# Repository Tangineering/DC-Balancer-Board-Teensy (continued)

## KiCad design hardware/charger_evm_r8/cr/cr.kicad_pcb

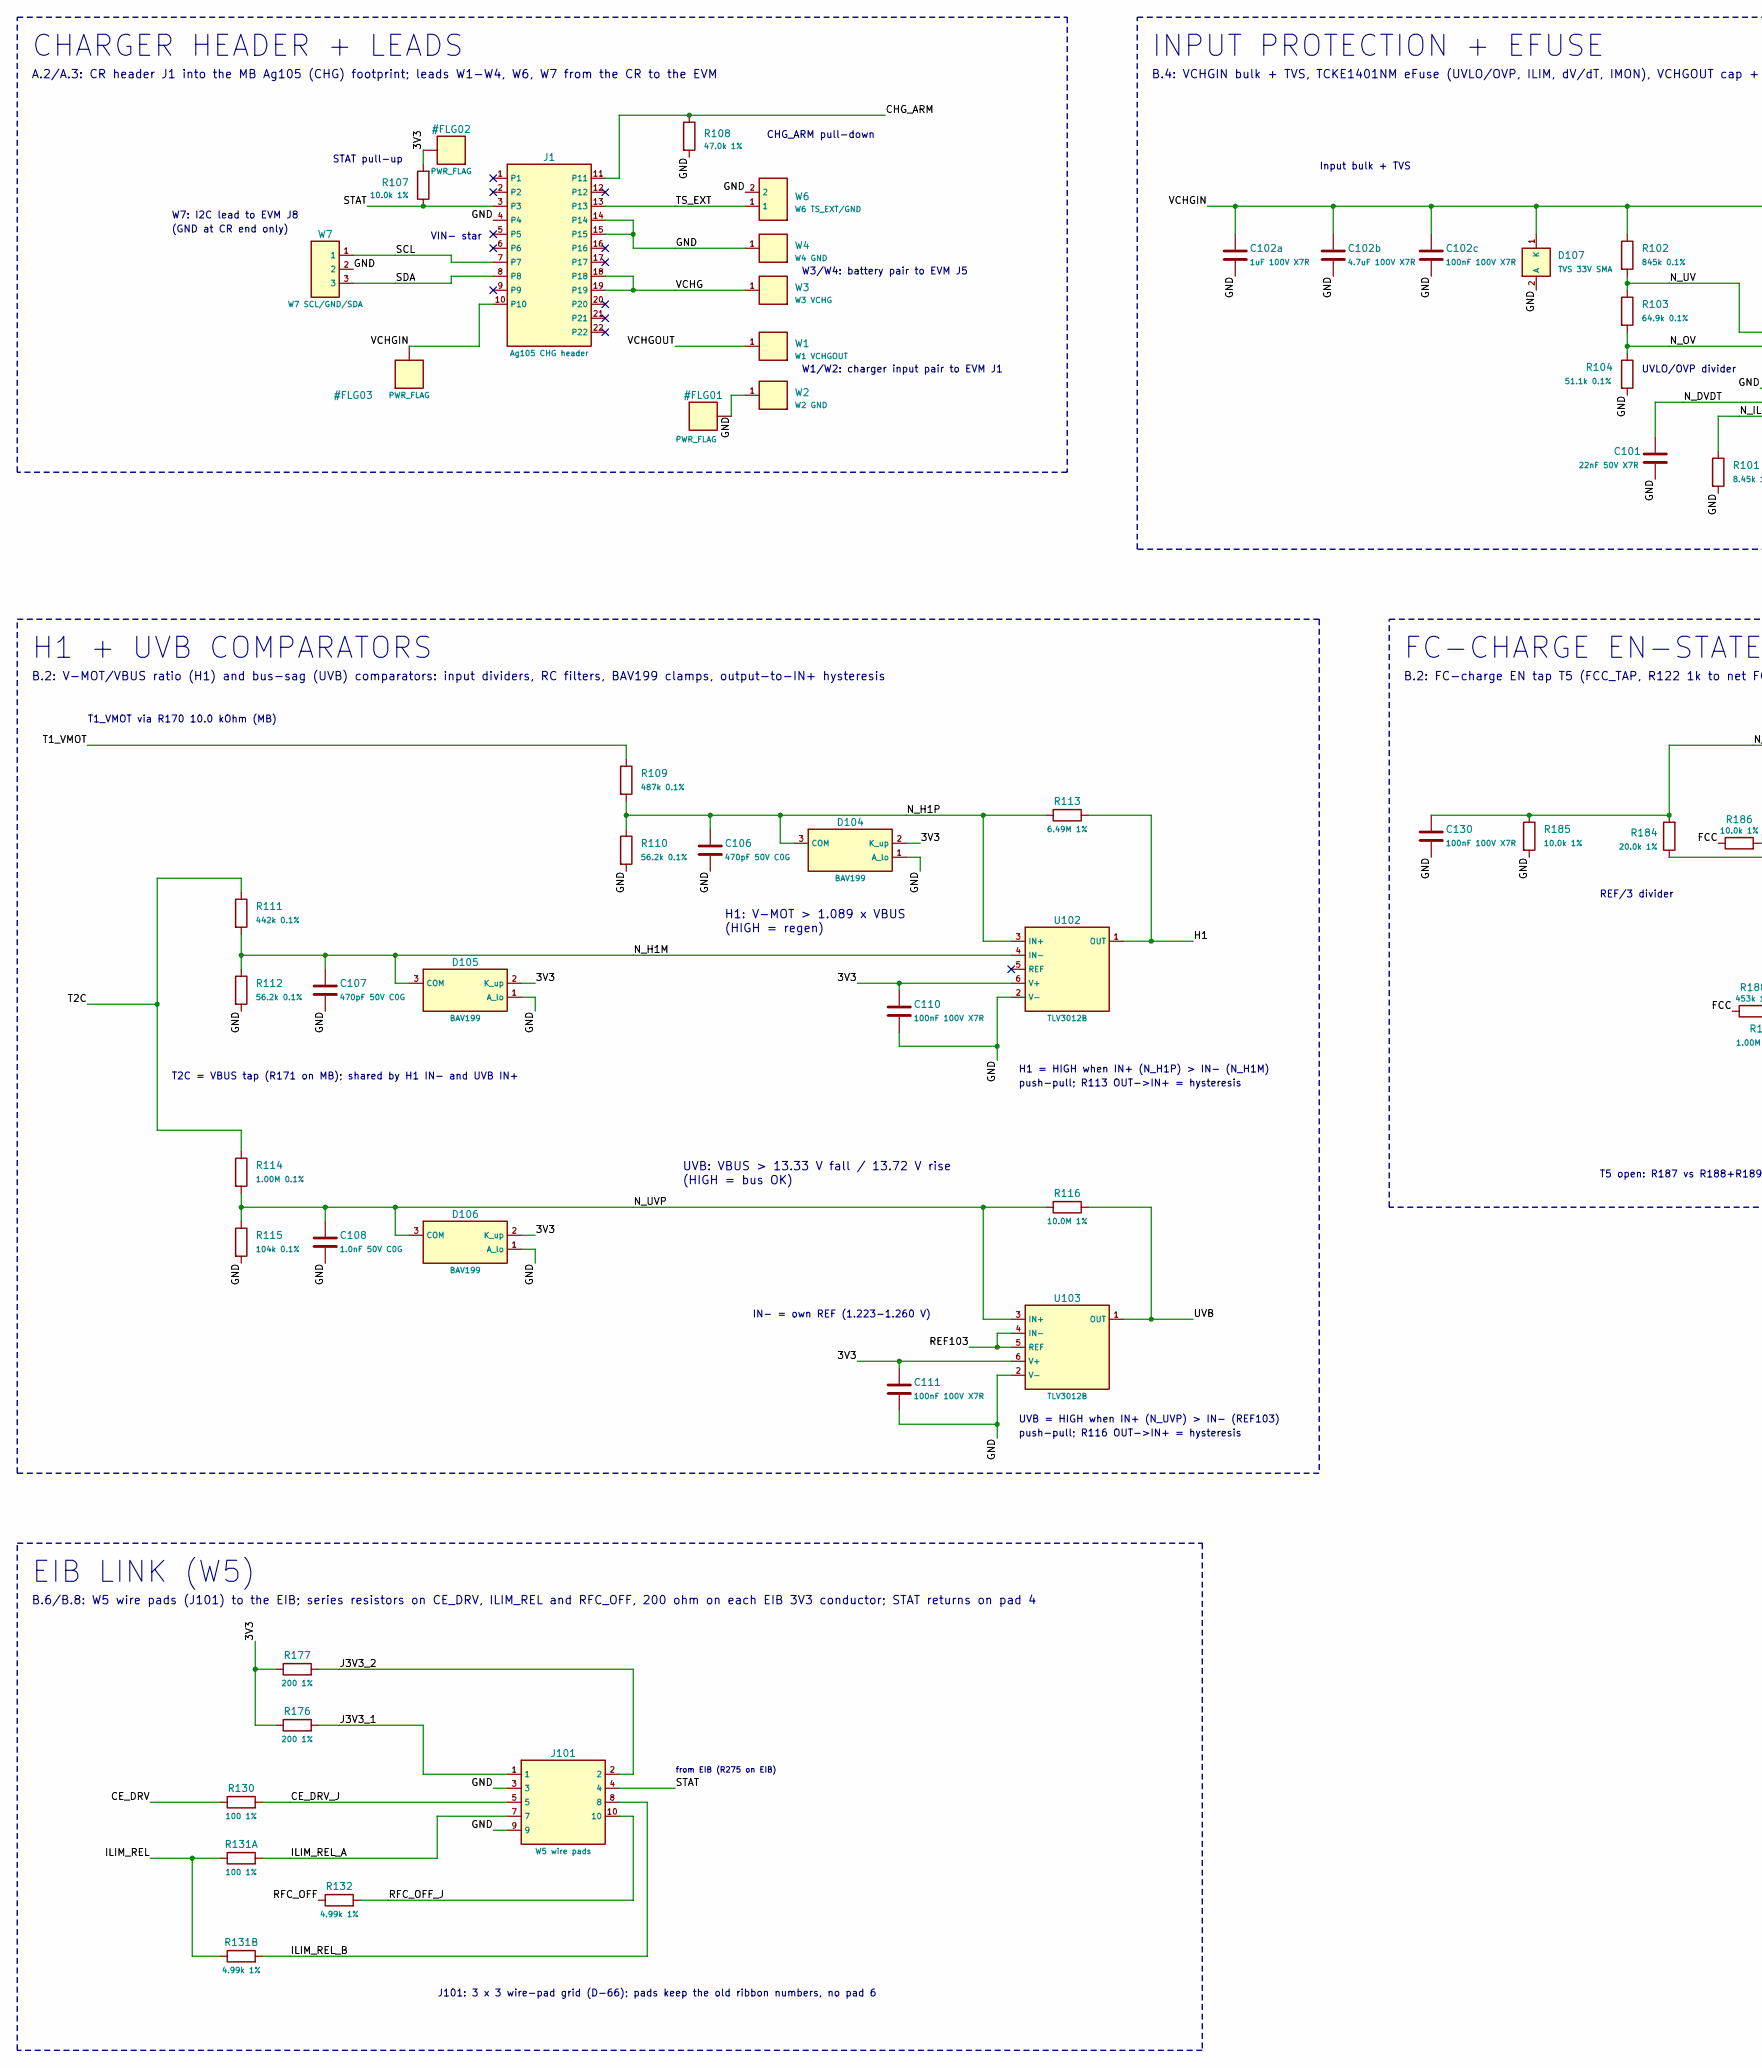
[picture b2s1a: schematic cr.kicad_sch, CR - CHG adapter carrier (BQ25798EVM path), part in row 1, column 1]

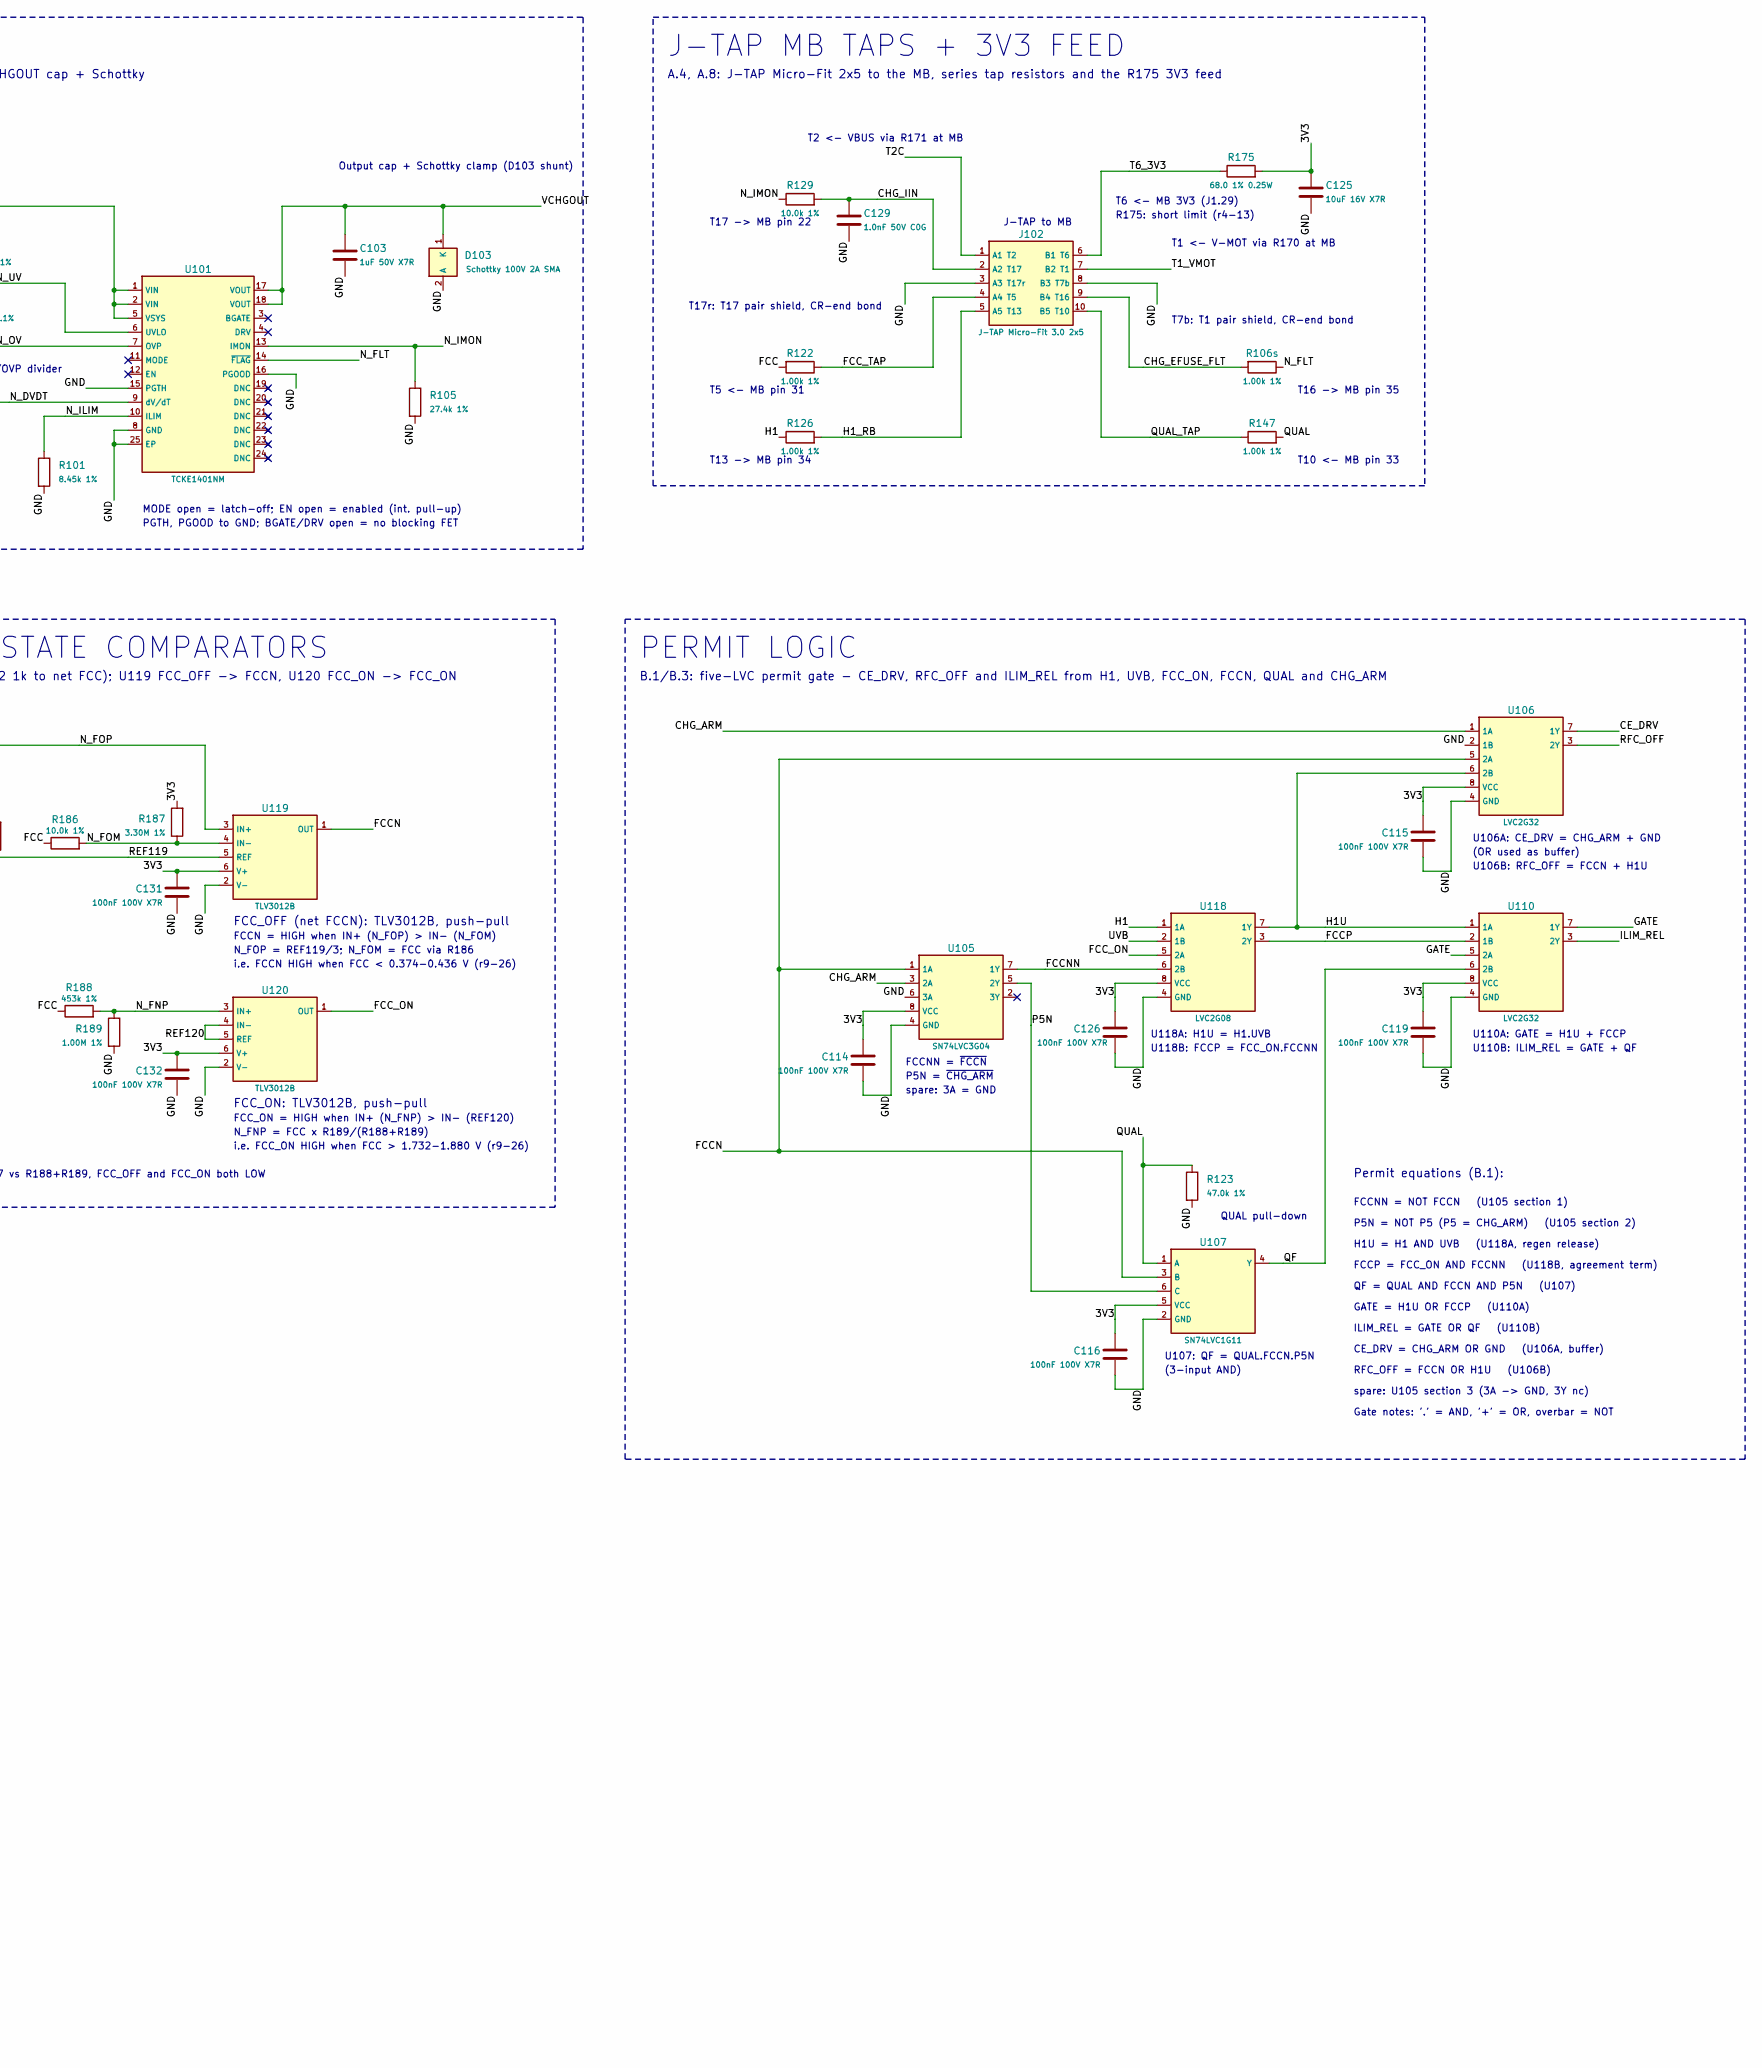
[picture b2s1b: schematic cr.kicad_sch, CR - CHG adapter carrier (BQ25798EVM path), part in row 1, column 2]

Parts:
C101: 22nF 50V X7R; C_0603_1608Metric_CrtYd0.25; MPN C0603C223K5RACTU
C102a: 1uF 100V X7R; C_1206_3216Metric_CrtYd0.25; MPN CL31B105KCHSFNE
C102b: 4.7uF 100V X7R; C_1210_3225Metric_CrtYd0.25; MPN CNC6P1X7R2A475K250AE
C102c, C110, C111, C114, C115, C116, C119, C126, C130, C131, C132: 100nF 100V X7R; C_0603_1608Metric_CrtYd0.25; MPN GRM188R72A104KA35D
C103: 1uF 50V X7R; C_0805_2012Metric_CrtYd0.25; MPN CL21B105KBFNNNF
C106, C107: 470pF 50V C0G; C_0603_1608Metric_CrtYd0.25; MPN GRM1885C1H471JA01D
C108, C129: 1.0nF 50V C0G; C_0603_1608Metric_CrtYd0.25; MPN GRM1885C1H102JA01D
C125: 10uF 16V X7R; C_0805_2012Metric_CrtYd0.25; MPN CL21B106KOQNNNE
D103: Schottky 100V 2A SMA; D_SMA_CrtYd0.25; MPN STPS2H100A
D104, D105, D106: BAV199; SOT-23_CrtYd0.25; MPN BAV199-7-F
D107: TVS 33V SMA; D_SMA_CrtYd0.25; MPN SMAJ33A
J1: Ag105 CHG header; Ag105_CHG_Carrier_22pin_P2.54mm; MPN TSW-110-07-L-S + TSW-112-07-L-S
J101: W5 wire pads; WirePads_PTH_3x3_D1.0mm_Pad1.8mm_P2.54mm_CrtYd0.25
J102: J-TAP Micro-Fit 3.0 2x5; Molex_Micro-Fit_3.0_43045-1012_2x05_P3.00mm_Vertical_CrtYd0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; MPN 43045-1012
R101: 8.45k 1%; R_0603_1608Metric_CrtYd0.25; MPN CRCW06038K45FKEA
R102: 845k 0.1%; R_0805_2012Metric_CrtYd0.25; MPN ERA-6AEB8453V
R103: 64.9k 0.1%; R_0603_1608Metric_CrtYd0.25; MPN ERA-3AEB6492V
R104: 51.1k 0.1%; R_0603_1608Metric_CrtYd0.25; MPN TNPW060351K1BEEA
R105: 27.4k 1%; R_0603_1608Metric_CrtYd0.25; MPN CRCW060327K4FKEA
R106s, R122, R126, R147: 1.00k 1%; R_0603_1608Metric_CrtYd0.25; MPN CRCW06031K00FKEA
R107, R129, R185, R186: 10.0k 1%; R_0603_1608Metric_CrtYd0.25; MPN CRCW060310K0FKEA
R108, R123: 47.0k 1%; R_0603_1608Metric_CrtYd0.25; MPN CRCW060347K0FKEA
R109: 487k 0.1%; R_0805_2012Metric_CrtYd0.25; MPN ERA-6AEB4873V
R110, R112: 56.2k 0.1%; R_0603_1608Metric_CrtYd0.25; MPN ERA-3AEB5622V
R111: 442k 0.1%; R_0805_2012Metric_CrtYd0.25; MPN TNPW0805442KBEEA
R113: 6.49M 1%; R_0603_1608Metric_CrtYd0.25; MPN CRCW06036M49FKEA
R114: 1.00M 0.1%; R_0805_2012Metric_CrtYd0.25; MPN TNPW08051M00BEEA
R115: 104k 0.1%; R_0603_1608Metric_CrtYd0.25; MPN RT0603BRD07104KL
R116: 10.0M 1%; R_0603_1608Metric_CrtYd0.25; MPN CRCW060310M0FKEA
R130, R131A: 100 1%; R_0603_1608Metric_CrtYd0.25; MPN CRCW0603100RFKEA
R131B, R132: 4.99k 1%; R_0603_1608Metric_CrtYd0.25; MPN CRCW06034K99FKEA
R175: 68.0 1% 0.25W; R_1206_3216Metric_CrtYd0.25; MPN CRCW120668R0FKEA
R176, R177: 200 1%; R_0603_1608Metric_CrtYd0.25; MPN CRCW0603200RFKEA
R184: 20.0k 1%; R_0603_1608Metric_CrtYd0.25; MPN CRCW060320K0FKEA
R187: 3.30M 1%; R_0603_1608Metric_CrtYd0.25; MPN CRCW06033M30FKEA
R188: 453k 1%; R_0603_1608Metric_CrtYd0.25; MPN CRCW0603453KFKEA
R189: 1.00M 1%; R_0603_1608Metric_CrtYd0.25; MPN CRCW06031M00FKEA
U101: TCKE1401NM; TPS26630_RGE0024_VQFN-24_4x4mm_P0.5mm_ThermalVias_CrtYd0.25; MPN TCKE1401NM,R1F
U102, U103, U119, U120: TLV3012B; SOT-23-6_CrtYd0.25; MPN TLV3012BIDBVR
U105: SN74LVC3G04; Texas_DCT0008A_SSOP-8_TI-land_CrtYd0.25; MPN SN74LVC3G04DCTR
U106, U110: LVC2G32; Texas_DCT0008A_SSOP-8_TI-land_CrtYd0.25; MPN SN74LVC2G32DCTR
U107: SN74LVC1G11; SOT-23-6_CrtYd0.25; MPN SN74LVC1G11DBVR
U118: LVC2G08; Texas_DCT0008A_SSOP-8_TI-land_CrtYd0.25; MPN SN74LVC2G08IDCTRQ1
W1: W1 VCHGOUT; LeadPad_PTH_D1.3mm_Pad2.3mm_CrtYd0.25
W2: W2 GND; LeadPad_PTH_D1.3mm_Pad2.3mm_CrtYd0.25
W3: W3 VCHG; LeadPad_PTH_D1.5mm_Pad2.5mm_CrtYd0.25
W4: W4 GND; LeadPad_PTH_D1.5mm_Pad2.5mm_CrtYd0.25
W6: W6 TS_EXT/GND; LeadPads_PTH_1x02_D1.0mm_Pad1.8mm_P2.54mm_Placeholder
W7: W7 SCL/GND/SDA; LeadPads_PTH_1x03_D1.0mm_Pad1.8mm_P2.54mm_Placeholder

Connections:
/3V3: C110.1, C111.1, C114.1, C115.1, C116.1, C119.1, C125.1, C126.1, C131.1, C132.1, D104.2 (K_up), D105.2 (K_up), D106.2 (K_up), R107.2, R175.2, R176.1, R177.1, R187.2, U102.6 (V+), U103.6 (V+), U105.8 (VCC), U106.8 (VCC), U107.5 (VCC), U110.8 (VCC), U118.8 (VCC), U119.6 (V+), U120.6 (V+)
/CE_DRV: R130.1, U106.7 (1Y)
/CE_DRV_J: J101.5, R130.2
/CHG_ARM: J1.11, R108.1, U105.3 (2A), U106.1 (1A)
/CHG_EFUSE_FLT: J102.9 (B4 T16), R106s.2
/CHG_IIN: C129.1, J102.2 (A2 T17), R129.2
/FCC: R122.2, R186.1, R188.1
/FCCN: U105.1 (1A), U106.5 (2A), U107.3 (B), U119.1 (OUT)
/FCCNN: U105.7 (1Y), U118.6 (2B)
/FCCP: U110.2 (1B), U118.3 (2Y)
/FCC_ON: U118.5 (2A), U120.1 (OUT)
/FCC_TAP: J102.4 (A4 T5), R122.1
/GATE: U110.5 (2A), U110.7 (1Y)
/GND: C101.2, C102a.2, C102b.2, C102c.2, C103.2, C106.2, C107.2, C108.2, C110.2, C111.2, C114.2, C115.2, C116.2, C119.2, C125.2, C126.2, C129.2, C130.2, C131.2, C132.2, D103.2 (A), D104.1 (A_lo), D105.1 (A_lo), D106.1 (A_lo), D107.2 (A), J1.4, J1.14, J1.15, J101.3, J101.9, J102.3 (A3 T17r), J102.8 (B3 T7b), R101.2, R104.2, R105.2, R108.2, R110.2, R112.2, R115.2, R123.2, R185.2, R189.2, U101.8 (GND), U101.15 (PGTH), U101.16 (PGOOD), U101.25 (EP), U102.2 (V-), U103.2 (V-), U105.4 (GND), U105.6 (3A), U106.2 (1B), U106.4 (GND), U107.2 (GND), U110.4 (GND), U118.4 (GND), U119.2 (V-), U120.2 (V-), W2.1, W4.1, W6.2, W7.2
/H1: R113.1, R126.1, U102.1 (OUT), U118.1 (1A)
/H1U: U106.6 (2B), U110.1 (1A), U118.7 (1Y)
/H1_RB: J102.5 (A5 T13), R126.2
/ILIM_REL: R131A.1, R131B.1, U110.3 (2Y)
/ILIM_REL_A: J101.7, R131A.2
/ILIM_REL_B: J101.8, R131B.2
/J3V3_1: J101.1, R176.2
/J3V3_2: J101.2, R177.2
/N_DVDT: C101.1, U101.9 (dV/dT)
/N_FLT: R106s.1, U101.14 (~FLAG)
/N_FNP: R188.2, R189.1, U120.3 (IN+)
/N_FOM: R186.2, R187.1, U119.4 (IN-)
/N_FOP: C130.1, R184.2, R185.1, U119.3 (IN+)
/N_H1M: C107.1, D105.3 (COM), R111.2, R112.1, U102.4 (IN-)
/N_H1P: C106.1, D104.3 (COM), R109.2, R110.1, R113.2, U102.3 (IN+)
/N_ILIM: R101.1, U101.10 (ILIM)
/N_IMON: R105.1, R129.1, U101.13 (IMON)
/N_OV: R103.2, R104.1, U101.7 (OVP)
/N_UV: R102.2, R103.1, U101.6 (UVLO)
/N_UVP: C108.1, D106.3 (COM), R114.2, R115.1, R116.2, U103.3 (IN+)
/P5N: U105.5 (2Y), U107.6 (C)
/QF: U107.4 (Y), U110.6 (2B)
/QUAL: R123.1, R147.2, U107.1 (A)
/QUAL_TAP: J102.10 (B5 T10), R147.1
/REF103: U103.4 (IN-), U103.5 (REF)
/REF119: R184.1, U119.5 (REF)
/REF120: U120.4 (IN-), U120.5 (REF)
/RFC_OFF: R132.1, U106.3 (2Y)
/RFC_OFF_J: J101.10, R132.2
/SCL: J1.7, W7.1
/SDA: J1.8, W7.3
/STAT: J1.3, J101.4, R107.1
/T1_VMOT: J102.7 (B2 T1), R109.1
/T2C: J102.1 (A1 T2), R111.1, R114.1
/T6_3V3: J102.6 (B1 T6), R175.1
/TS_EXT: J1.13, W6.1
/UVB: R116.1, U103.1 (OUT), U118.2 (1B)
/VCHG: J1.18, J1.19, W3.1
/VCHGIN: C102a.1, C102b.1, C102c.1, D107.1 (K), J1.10, R102.1, U101.1 (VIN), U101.2 (VIN), U101.5 (VSYS)
/VCHGOUT: C103.1, D103.1 (K), U101.17 (VOUT), U101.18 (VOUT), W1.1

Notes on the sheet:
CHARGER HEADER + LEADS
A.2/A.3: CR header J1 into the MB Ag105 (CHG) footprint; leads W1-W4, W6, W7 from the CR to the EVM
STAT pull-up
CHG_ARM pull-down
W7: I2C lead to EVM J8
(GND at CR end only)
W1/W2: charger input pair to EVM J1
W3/W4: battery pair to EVM J5
VIN- star
INPUT PROTECTION + EFUSE
B.4: VCHGIN bulk + TVS, TCKE1401NM eFuse (UVLO/OVP, ILIM, dV/dT, IMON), VCHGOUT cap + Schottky
Input bulk + TVS
UVLO/OVP divider
Output cap + Schottky clamp (D103 shunt)
MODE open = latch-off; EN open = enabled (int. pull-up)
PGTH, PGOOD to GND; BGATE/DRV open = no blocking FET
H1 + UVB COMPARATORS
B.2: V-MOT/VBUS ratio (H1) and bus-sag (UVB) comparators: input dividers, RC filters, BAV199 clamps, output-to-IN+ hysteresis
H1: V-MOT > 1.089 x VBUS
(HIGH = regen)
UVB: VBUS > 13.33 V fall / 13.72 V rise
(HIGH = bus OK)
T2C = VBUS tap (R171 on MB); shared by H1 IN- and UVB IN+
T1_VMOT via R170 10.0 kOhm (MB)
IN- = own REF (1.223-1.260 V)
H1 = HIGH when IN+ (N_H1P) > IN- (N_H1M)
push-pull; R113 OUT->IN+ = hysteresis
UVB = HIGH when IN+ (N_UVP) > IN- (REF103)
push-pull; R116 OUT->IN+ = hysteresis
FC-CHARGE EN-STATE COMPARATORS
B.2: FC-charge EN tap T5 (FCC_TAP, R122 1k to net FCC); U119 FCC_OFF -> FCCN, U120 FCC_ON -> FCC_ON
FCC_OFF (net FCCN): TLV3012B, push-pull
FCCN = HIGH when IN+ (N_FOP) > IN- (N_FOM)
N_FOP = REF119/3; N_FOM = FCC via R186
i.e. FCCN HIGH when FCC < 0.374-0.436 V (r9-26)
FCC_ON: TLV3012B, push-pull
FCC_ON = HIGH when IN+ (N_FNP) > IN- (REF120)
N_FNP = FCC x R189/(R188+R189)
i.e. FCC_ON HIGH when FCC > 1.732-1.880 V (r9-26)
REF/3 divider

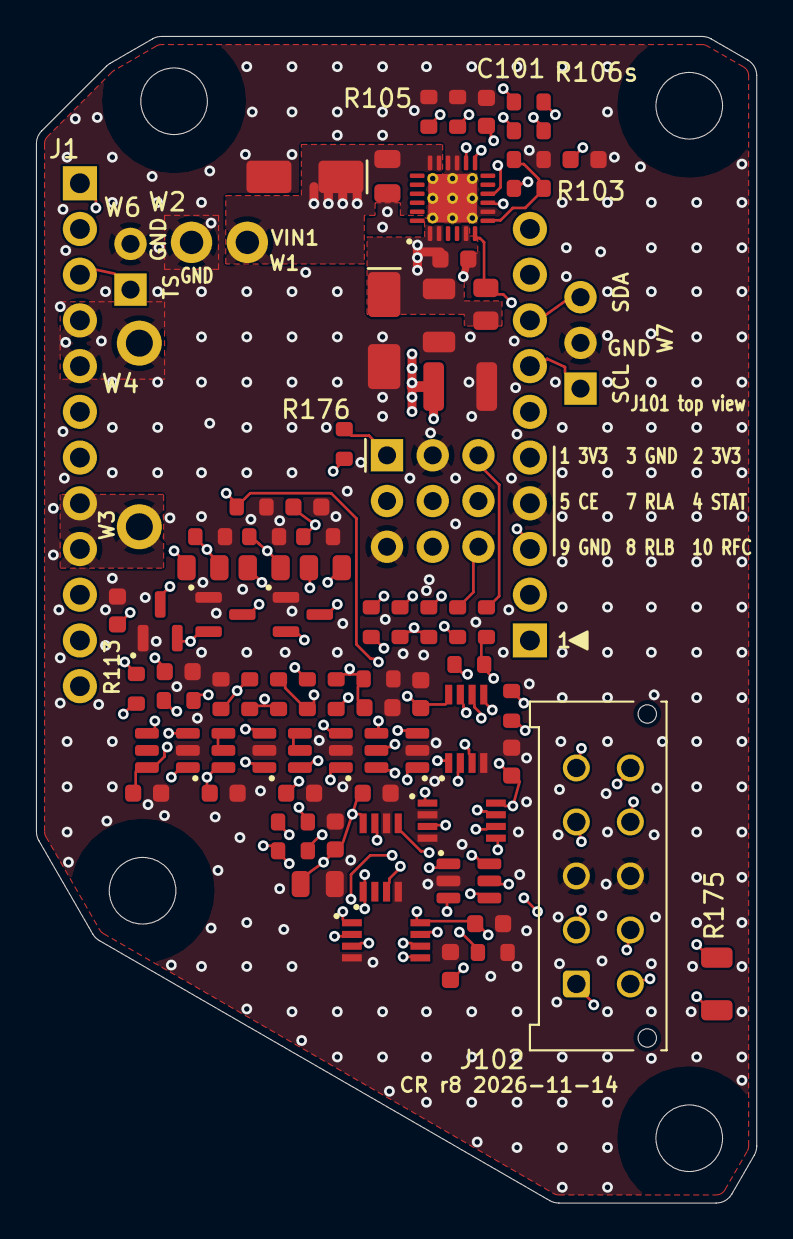
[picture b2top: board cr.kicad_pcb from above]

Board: 4 copper layers, 40.0 x 64.8 mm, 82 parts (0 on the bottom side), 54 nets.

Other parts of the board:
MH1, MH2, MH3, MH4: 6-32 hole 3.70 mm
